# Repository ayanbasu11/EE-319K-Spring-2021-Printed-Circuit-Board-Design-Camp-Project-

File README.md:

# EE-319K-Spring-2021-Printed-Circuit-Board-Design-Camp-Project-
This hands-on course will walk through the process of PCB design, layout, construction, and test. Each team of two or three students will layout an EE319K/EE319H PCB that contains all the circuits required to complete Labs 6, 7, 8, and 10. The circuit design and software will be presented as part of regular EE319K/EE319H, but in this camp, students will manufacture the interconnections as a printed circuit board. Students will translate the electrical circuit into a PCB design, where most of their parts are selected from a starter file containing the parts already in your EE319K/EE319H lab kit. Students will learn to consider issues like drill holes, high current routing, standard values, tolerances, and testing. Students draw the electrical circuits in schematic form as the first assignment, performed individually. If you complete assignment 1 by Wednesday 10am, teams of 2 or 3 will be formed and the team will create one PCB design. Teams who complete their PCB layout by Friday 3/19 10am will have their board manufactured, making three copies. There are two 20-pin headers and some hardware that will be distributed with the PCBs. Since all students will create similar circuits, students will evaluate each other’s layout. It takes about 2 weeks to get PCB boards produced, so the PCBs should be back in time for you to use it in Labs 8, 9, and 10. To use the PCB for EE319K/EE319H you will need to solder the kit components onto the PCB.

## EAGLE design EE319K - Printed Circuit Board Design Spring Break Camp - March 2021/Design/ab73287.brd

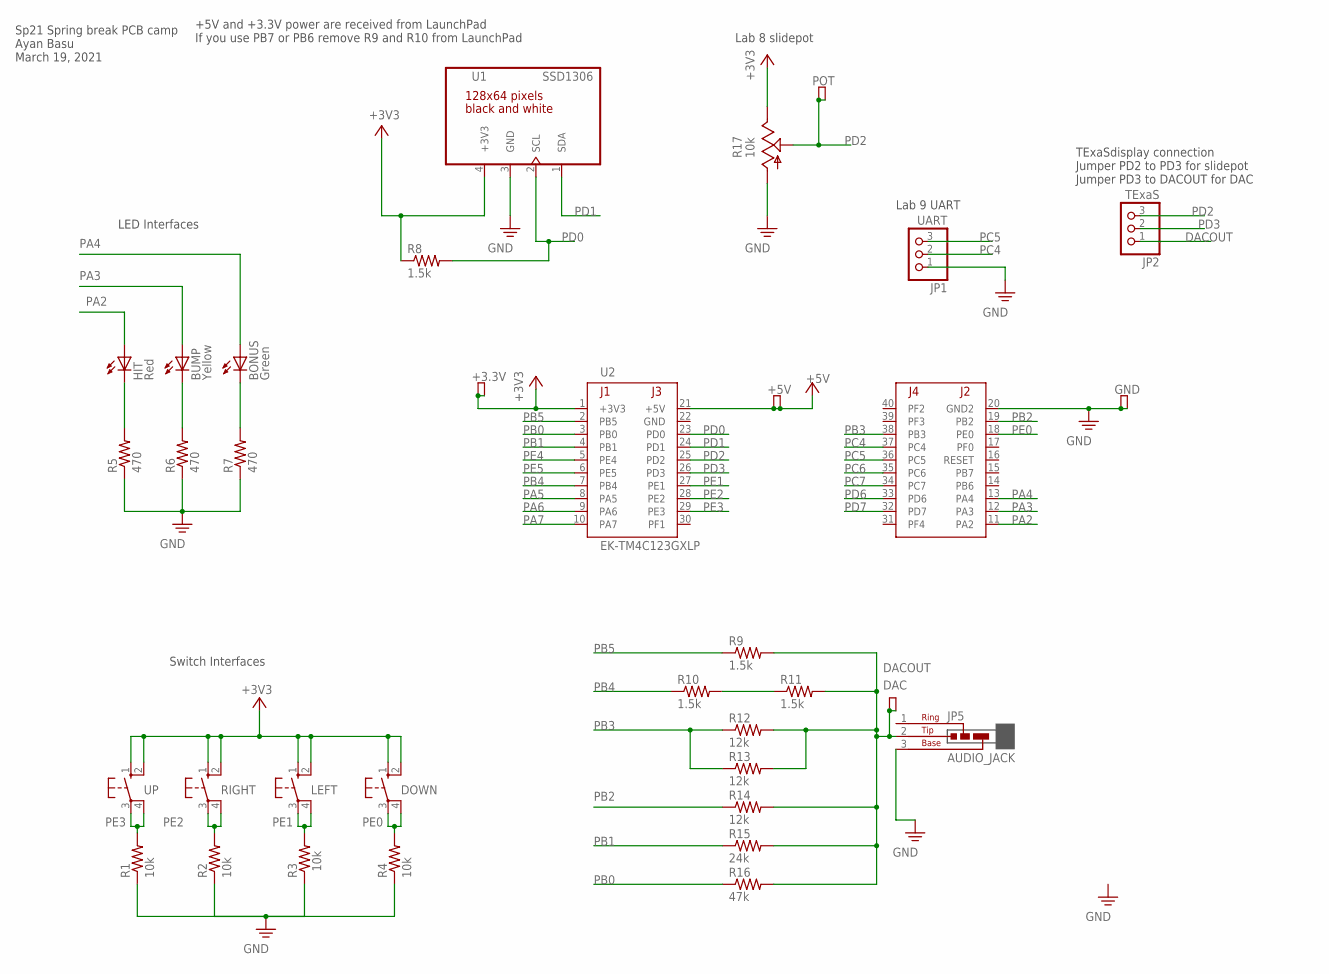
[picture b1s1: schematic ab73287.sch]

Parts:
+3.3V, +5V: TP2
BONUS: Green; LED5MM
BUMP: Yellow; LED5MM
DAC: TP2
DOWN: B3F-1052; B3F-10XX
GND: TP2
HIT: Red; LED5MM
JP1: UART; 1X03
JP2: TExaS; 1X03
JP5: AUDIO_JACK; JACK
LEFT: B3F-1052; B3F-10XX
POT: TP2
R1, R2, R3, R4: 10k; RES300MIL
R5, R6, R7: 470; RES300MIL
R8, R9, R10, R11: 1.5k; RES300MIL
R12, R13, R14: 12k; RES300MIL
R15: 24k; RES300MIL
R16: 47k; RES300MIL
R17: 10k; B25U
RIGHT: B3F-1052; B3F-10XX
U1: SSD1306
U2: EK-TM4C123GXLP; TM4C123LAUNCHPAD
UP: B3F-1052; B3F-10XX

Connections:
+3V3: +3.3V.MP (TPA), +3.3V.MP1 (TPB), DOWN.1 (S), DOWN.2 (S1), LEFT.1 (S), LEFT.2 (S1), R8.1, R17.1 (E), RIGHT.1 (S), RIGHT.2 (S1), U1.4 (+3V3), U2.1 (+3V3), UP.1 (S), UP.2 (S1)
+5V: +5V.MP (TPA), +5V.MP1 (TPB), U2.21 (+5V)
BIT4: R10.2, R11.1
DACOUT: DAC.MP (TPA), DAC.MP1 (TPB), JP2.1, JP5.2 (TIP), R9.2, R11.2, R12.2, R13.2, R14.2, R15.2, R16.2
GND: GND.MP (TPA), GND.MP1 (TPB), JP1.1, JP5.3 (BASE), R1.1, R2.1, R3.1, R4.1, R5.1, R6.1, R7.1, R17.3 (A), U1.3 (GND), U2.20 (GND2)
GREEN: BONUS.K (C), R7.2
PA2: HIT.A, U2.11 (PA2)
PA3: BUMP.A, U2.12 (PA3)
PA4: BONUS.A, U2.13 (PA4)
PA5: U2.8 (PA5)
PA6: U2.9 (PA6)
PA7: U2.10 (PA7)
PB0: R16.1, U2.3 (PB0)
PB1: R15.1, U2.4 (PB1)
PB2: R14.1, U2.19 (PB2)
PB3: R12.1, R13.1, U2.38 (PB3)
PB4: R10.1, U2.7 (PB4)
PB5: R9.1, U2.2 (PB5)
PC4: JP1.2, U2.37 (PC4)
PC5: JP1.3, U2.36 (PC5)
PC6: U2.35 (PC6)
PC7: U2.34 (PC7)
PD0: R8.2, U1.2 (SCL), U2.23 (PD0)
PD1: U1.1 (SDA), U2.24 (PD1)
PD2: JP2.3, POT.MP (TPA), POT.MP1 (TPB), R17.2 (S), U2.25 (PD2)
PD3: JP2.2, U2.26 (PD3)
PD6: U2.33 (PD6)
PD7: U2.32 (PD7)
PE0: DOWN.3, DOWN.4 (P1), R4.2, U2.18 (PE0)
PE1: LEFT.3, LEFT.4 (P1), R3.2, U2.27 (PE1)
PE2: R2.2, RIGHT.3, RIGHT.4 (P1), U2.28 (PE2)
PE3: R1.2, U2.29 (PE3), UP.3, UP.4 (P1)
PE4: U2.5 (PE4)
PE5: U2.6 (PE5)
RED: HIT.K (C), R5.2
YELLOW: BUMP.K (C), R6.2

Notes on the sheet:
Sp21 Spring break PCB camp Ayan Basu March 19, 2021
+5V and +3.3V power are received from LaunchPad If you use PB7 or PB6 remove R9 and R10 from LaunchPad
Switch Interfaces
LED Interfaces
TExaSdisplay connection Jumper PD2 to PD3 for slidepot Jumper PD3 to DACOUT for DAC
Lab 9 UART
Lab 8 slidepot

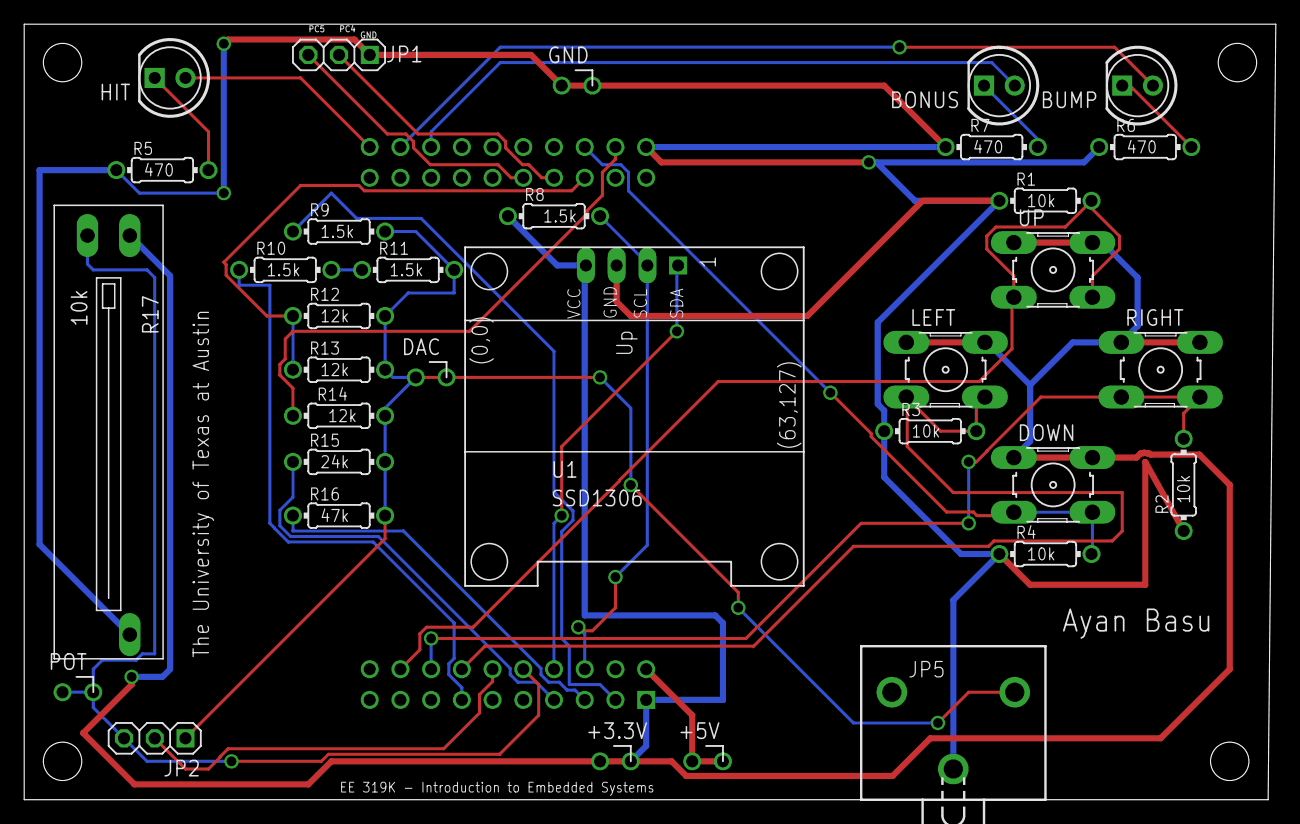
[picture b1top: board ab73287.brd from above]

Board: 2 copper layers, 103.5 x 64.1 mm, 34 parts (1 on the bottom side), 27 nets.
